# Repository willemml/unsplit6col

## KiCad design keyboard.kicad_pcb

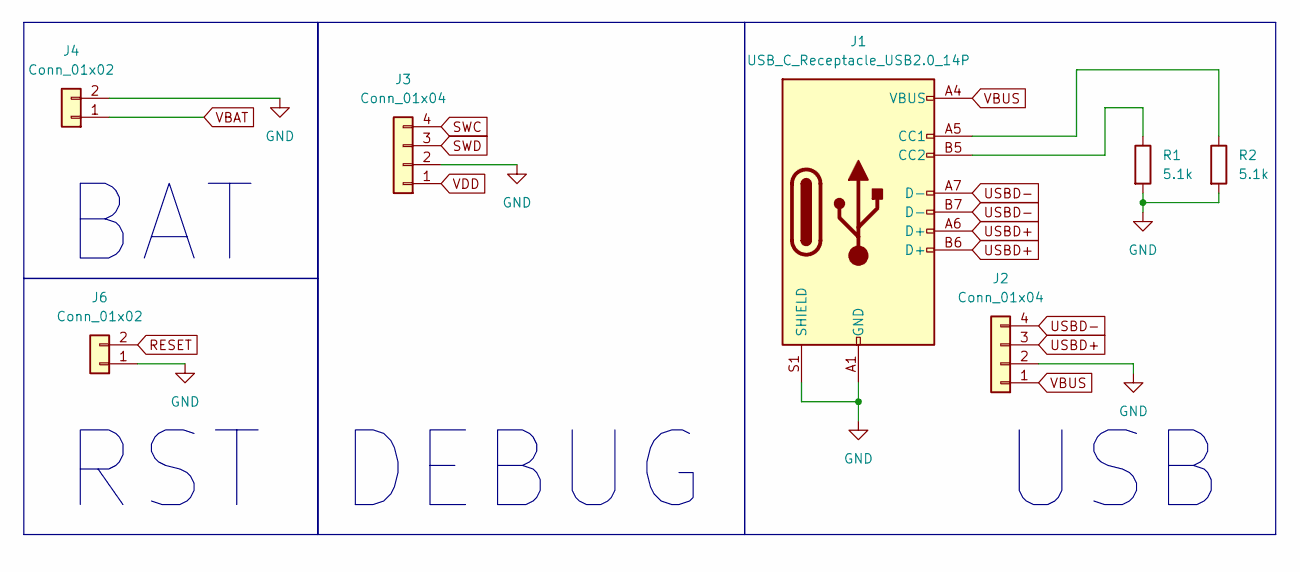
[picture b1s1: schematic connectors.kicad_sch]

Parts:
J1: USB_C_Receptacle_USB2.0_14P; USB_C_Receptacle_HCTL_HC-TYPE-C-16P-01A
J2, J3: Conn_01x04; PinHeader_1x04_P2.54mm_Vertical
J4, J6: Conn_01x02; PinHeader_1x02_P2.54mm_Vertical
R1, R2: 5.1k; R_0603_1608Metric

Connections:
GND: J1.A1 (GND), J1.A12 (GND), J1.B1 (GND), J1.B12 (GND), J1.S1 (SHIELD), J2.2, J3.2, J4.2, J6.1, R1.2, R2.2; also elsewhere on the board
unnamed: J1.A5 (CC1), R2.1
unnamed: J1.B5 (CC2), R1.1
RESET: J6.2; also elsewhere on the board
SWC: J3.4; also elsewhere on the board
SWD: J3.3; also elsewhere on the board
USBD+: J1.A6 (D+), J1.B6 (D+), J2.3; also elsewhere on the board
USBD-: J1.A7 (D-), J1.B7 (D-), J2.4; also elsewhere on the board
VBAT: J4.1; also elsewhere on the board
VBUS: J1.A4 (VBUS), J1.A9 (VBUS), J1.B4 (VBUS), J1.B9 (VBUS), J2.1; also elsewhere on the board
VDD: J3.1; also elsewhere on the board

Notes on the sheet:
USB
RST
BAT
DEBUG

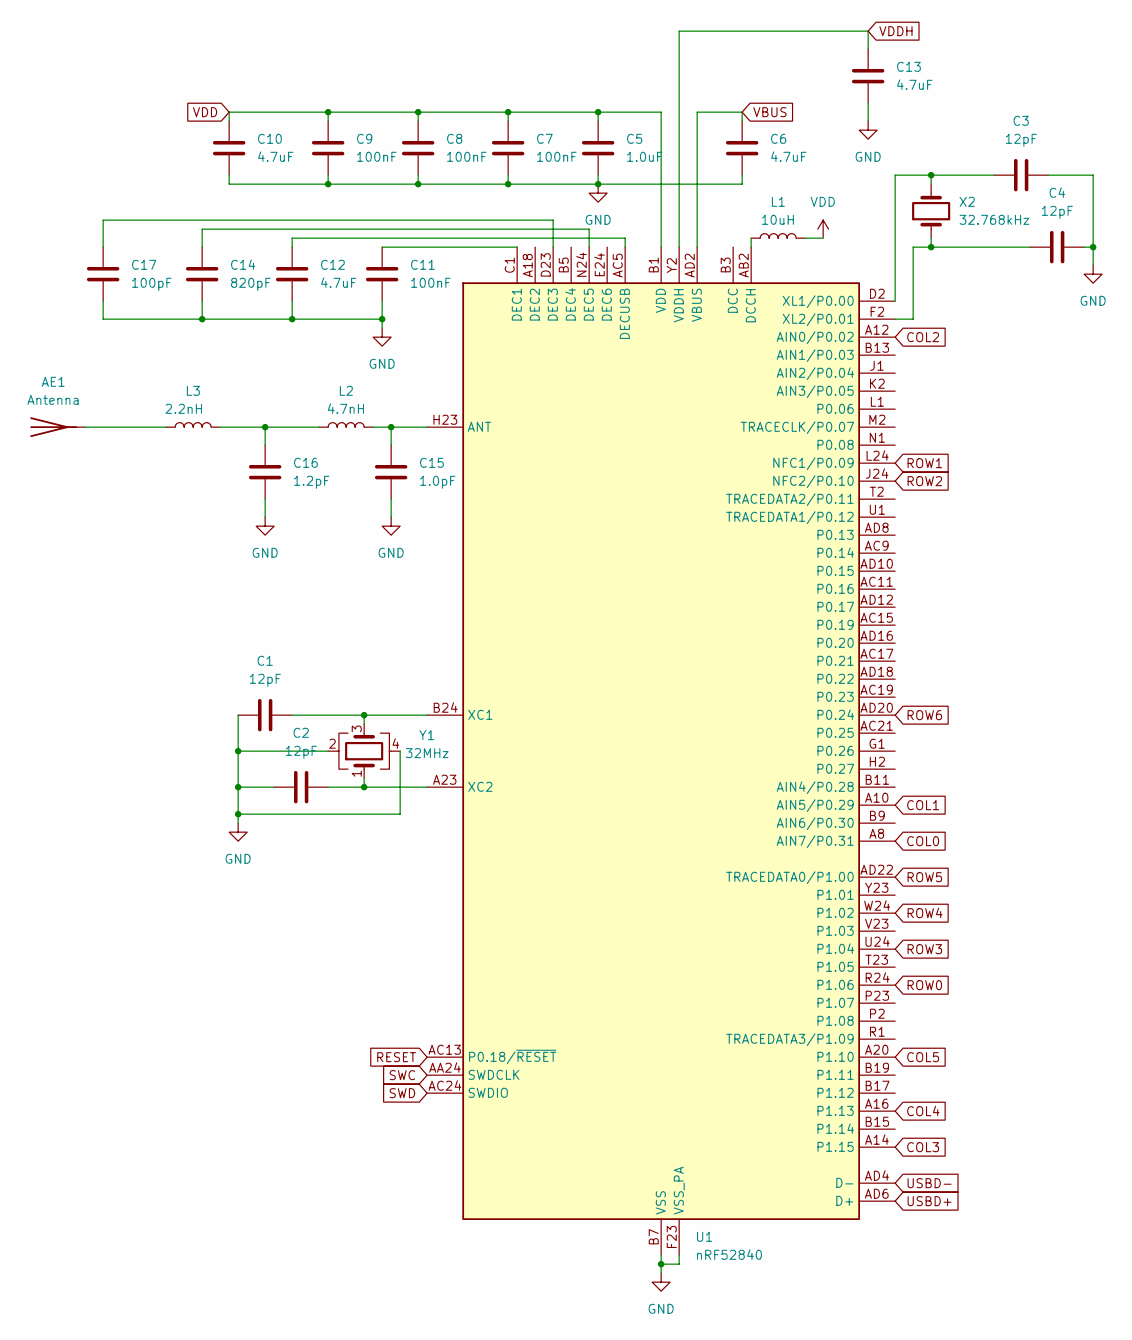
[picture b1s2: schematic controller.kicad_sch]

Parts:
AE1: Antenna; Texas_SWRA117D_2.4GHz_Left
C1, C2, C3, C4: 12pF; C_0603_1608Metric
C5: 1.0uF; C_0603_1608Metric
C6, C10, C12, C13: 4.7uF; C_0603_1608Metric
C7, C8, C9, C11: 100nF; C_0603_1608Metric
C14: 820pF; C_0603_1608Metric
C15: 1.0pF; C_0603_1608Metric
C16: 1.2pF; C_0603_1608Metric
C17: 100pF; C_0603_1608Metric
L1: 10uH; L_0603_1608Metric
L2: 4.7nH; L_0603_1608Metric
L3: 2.2nH; L_0603_1608Metric
U1: nRF52840; Nordic_AQFN-73-1EP_7x7mm_P0.5mm
X2: 32.768kHz; Crystal_SMD_0603-2Pin_6.0x3.5mm; LCSC C182057
Y1: 32MHz; Crystal_SMD_2016-4Pin_2.0x1.6mm; LCSC C2965582

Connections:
COL0: U1.A8 (AIN7/P0.31); also elsewhere on the board
COL1: U1.A10 (AIN5/P0.29); also elsewhere on the board
COL2: U1.A12 (AIN0/P0.02); also elsewhere on the board
COL3: U1.A14 (P1.15); also elsewhere on the board
COL4: U1.A16 (P1.13); also elsewhere on the board
COL5: U1.A20 (P1.10); also elsewhere on the board
GND: C1.1, C2.1, C3.2, C4.2, C5.2, C6.2, C7.2, C8.2, C9.2, C10.2, C11.2, C12.2, C13.2, C14.2, C15.2, C16.2, C17.2, U1.B7 (VSS), U1.EP (VSS), U1.F23 (VSS_PA), Y1.2, Y1.4; also elsewhere on the board
unnamed: AE1.1 (A), L3.1
unnamed: C16.1, L2.1, L3.2
unnamed: C15.1, L2.2, U1.H23 (ANT)
unnamed: L1.1, U1.AB2 (DCCH)
unnamed: C11.1, U1.C1 (DEC1)
unnamed: C17.1, U1.D23 (DEC3)
unnamed: C14.1, U1.N24 (DEC5)
unnamed: C12.1, U1.AC5 (DECUSB)
unnamed: C1.2, U1.B24 (XC1), Y1.3
unnamed: C2.2, U1.A23 (XC2), Y1.1
unnamed: C3.1, U1.D2 (XL1/P0.00), X2.2
unnamed: C4.1, U1.F2 (XL2/P0.01), X2.1
RESET: U1.AC13 (P0.18/~RESET); also elsewhere on the board
ROW0: U1.R24 (P1.06); also elsewhere on the board
ROW1: U1.L24 (NFC1/P0.09); also elsewhere on the board
ROW2: U1.J24 (NFC2/P0.10); also elsewhere on the board
ROW3: U1.U24 (P1.04); also elsewhere on the board
ROW4: U1.W24 (P1.02); also elsewhere on the board
ROW5: U1.AD22 (TRACEDATA0/P1.00); also elsewhere on the board
ROW6: U1.AD20 (P0.24); also elsewhere on the board
SWC: U1.AA24 (SWDCLK); also elsewhere on the board
SWD: U1.AC24 (SWDIO); also elsewhere on the board
USBD+: U1.AD6 (D+); also elsewhere on the board
USBD-: U1.AD4 (D-); also elsewhere on the board
VBUS: C6.1, U1.AD2 (VBUS); also elsewhere on the board
VDD: C5.1, C7.1, C8.1, C9.1, C10.1, L1.2, U1.A22 (VDD), U1.AD14 (VDD), U1.AD23 (VDD), U1.B1 (VDD), U1.W1 (VDD); also elsewhere on the board
VDDH: C13.1, U1.Y2 (VDDH); also elsewhere on the board

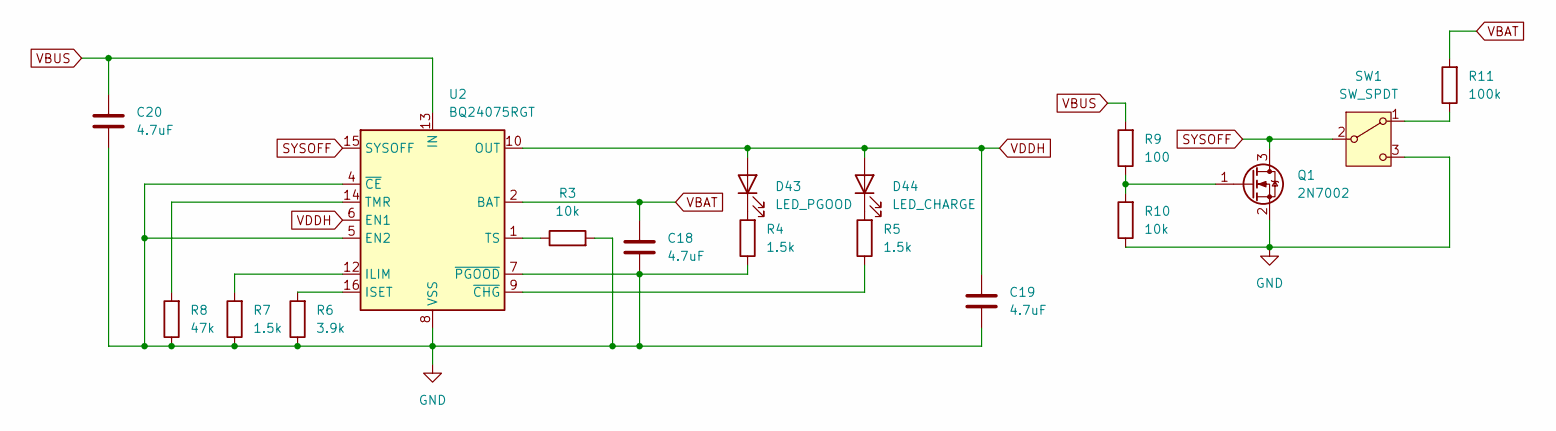
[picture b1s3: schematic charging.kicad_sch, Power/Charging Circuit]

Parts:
C18, C19, C20: 4.7uF; C_0603_1608Metric
D43: LED_PGOOD; LED_0603_1608Metric
D44: LED_CHARGE; LED_0603_1608Metric
Q1: 2N7002; SOT-23
R3, R10: 10k; R_0603_1608Metric
R4, R5, R7: 1.5k; R_0603_1608Metric
R6: 3.9k; R_0603_1608Metric
R8: 47k; R_0603_1608Metric
R9: 100; R_0603_1608Metric
R11: 100k; R_0603_1608Metric
SW1: SW_SPDT; SW_SPDT_PCM12; LCSC C431541
U2: BQ24075RGT; VQFN-16-1EP_3x3mm_P0.5mm_EP1.6x1.6mm

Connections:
GND: C18.2, C19.2, C20.2, Q1.2 (S), R3.2, R4.1, R6.1, R7.1, R8.1, R10.1, SW1.3 (C), U2.4 (~CE), U2.5 (EN2), U2.7 (~PGOOD), U2.8 (VSS), U2.17 (VSS); also elsewhere on the board
unnamed: D43.1 (K), R4.2
unnamed: D44.1 (K), R5.2
unnamed: Q1.1 (G), R9.1, R10.2
unnamed: R11.1, SW1.1 (A)
unnamed: R7.2, U2.12 (ILIM)
unnamed: R6.2, U2.16 (ISET)
unnamed: R8.2, U2.14 (TMR)
unnamed: R3.1, U2.1 (TS)
unnamed: R5.1, U2.9 (~CHG)
SYSOFF: Q1.3 (D), SW1.2 (B), U2.15 (SYSOFF)
VBAT: C18.1, R11.2, U2.2 (BAT), U2.3 (BAT); also elsewhere on the board
VBUS: C20.1, R9.2, U2.13 (IN); also elsewhere on the board
VDDH: C19.1, D43.2 (A), D44.2 (A), U2.6 (EN1), U2.10 (OUT), U2.11 (OUT); also elsewhere on the board

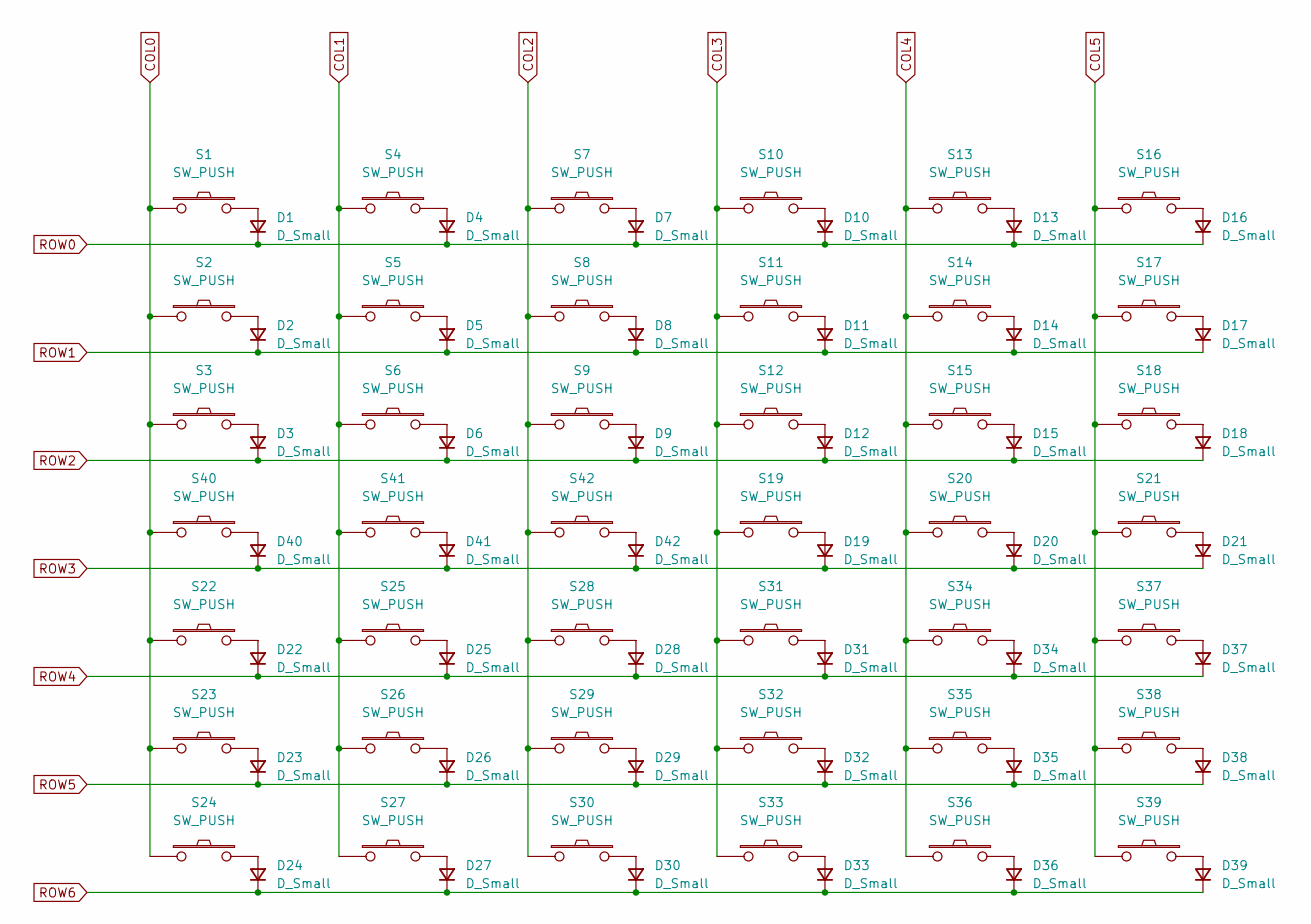
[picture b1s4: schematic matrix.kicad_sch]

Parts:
D1, D2, D3, D4, D5, D6, D7, D8, D9, D10, D11, D12, D13, D14, D15, D16, D17, D18, D19, D20, D21, D22, D23, D24, D25, D26, D27, D28, D29, D30, D31, D32, D33, D34, D35, D36, D37, D38, D39, D40, D41, D42: D_Small; D_SOD-123
S1: SW_PUSH; keyswitch_choc12_hotswap_1u; LCSC C5333465
S2, S3, S4, S5, S6, S7, S8, S9, S10, S11, S12, S13, S14, S15, S16, S17, S18, S19, S20, S21, S22, S23, S24, S25, S26, S27, S28, S29, S30, S31, S32, S33, S34, S35, S36, S37, S38, S39, S40, S41, S42: SW_PUSH; keyswitch_choc12_hotswap_1u

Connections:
COL0: S1.1, S2.1, S3.1, S22.1, S23.1, S24.1, S40.1; also elsewhere on the board
COL1: S4.1, S5.1, S6.1, S25.1, S26.1, S27.1, S41.1; also elsewhere on the board
COL2: S7.1, S8.1, S9.1, S28.1, S29.1, S30.1, S42.1; also elsewhere on the board
COL3: S10.1, S11.1, S12.1, S19.1, S31.1, S32.1, S33.1; also elsewhere on the board
COL4: S13.1, S14.1, S15.1, S20.1, S34.1, S35.1, S36.1; also elsewhere on the board
COL5: S16.1, S17.1, S18.1, S21.1, S37.1, S38.1, S39.1; also elsewhere on the board
unnamed: D1.2 (A), S1.2
unnamed: D2.2 (A), S2.2
unnamed: D3.2 (A), S3.2
unnamed: D4.2 (A), S4.2
unnamed: D5.2 (A), S5.2
unnamed: D6.2 (A), S6.2
unnamed: D7.2 (A), S7.2
unnamed: D8.2 (A), S8.2
unnamed: D9.2 (A), S9.2
unnamed: D10.2 (A), S10.2
unnamed: D11.2 (A), S11.2
unnamed: D12.2 (A), S12.2
unnamed: D13.2 (A), S13.2
unnamed: D14.2 (A), S14.2
unnamed: D15.2 (A), S15.2
unnamed: D16.2 (A), S16.2
unnamed: D17.2 (A), S17.2
unnamed: D18.2 (A), S18.2
unnamed: D19.2 (A), S19.2
unnamed: D20.2 (A), S20.2
unnamed: D21.2 (A), S21.2
unnamed: D22.2 (A), S22.2
unnamed: D23.2 (A), S23.2
unnamed: D24.2 (A), S24.2
unnamed: D25.2 (A), S25.2
unnamed: D26.2 (A), S26.2
unnamed: D27.2 (A), S27.2
unnamed: D28.2 (A), S28.2
unnamed: D29.2 (A), S29.2
unnamed: D30.2 (A), S30.2
unnamed: D31.2 (A), S31.2
unnamed: D32.2 (A), S32.2
unnamed: D33.2 (A), S33.2
unnamed: D34.2 (A), S34.2
unnamed: D35.2 (A), S35.2
unnamed: D36.2 (A), S36.2
unnamed: D37.2 (A), S37.2
unnamed: D38.2 (A), S38.2
unnamed: D39.2 (A), S39.2
unnamed: D40.2 (A), S40.2
unnamed: D41.2 (A), S41.2
unnamed: D42.2 (A), S42.2
ROW0: D1.1 (K), D4.1 (K), D7.1 (K), D10.1 (K), D13.1 (K), D16.1 (K); also elsewhere on the board
ROW1: D2.1 (K), D5.1 (K), D8.1 (K), D11.1 (K), D14.1 (K), D17.1 (K); also elsewhere on the board
ROW2: D3.1 (K), D6.1 (K), D9.1 (K), D12.1 (K), D15.1 (K), D18.1 (K); also elsewhere on the board
ROW3: D19.1 (K), D20.1 (K), D21.1 (K), D40.1 (K), D41.1 (K), D42.1 (K); also elsewhere on the board
ROW4: D22.1 (K), D25.1 (K), D28.1 (K), D31.1 (K), D34.1 (K), D37.1 (K); also elsewhere on the board
ROW5: D23.1 (K), D26.1 (K), D29.1 (K), D32.1 (K), D35.1 (K), D38.1 (K); also elsewhere on the board
ROW6: D24.1 (K), D27.1 (K), D30.1 (K), D33.1 (K), D36.1 (K), D39.1 (K); also elsewhere on the board

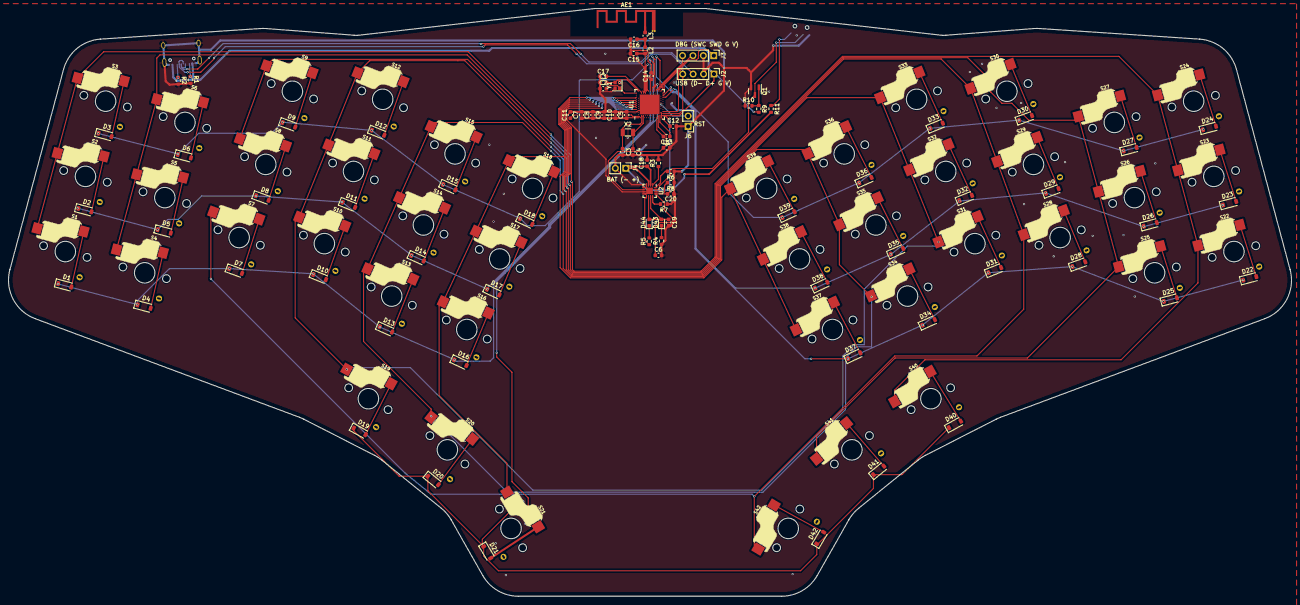
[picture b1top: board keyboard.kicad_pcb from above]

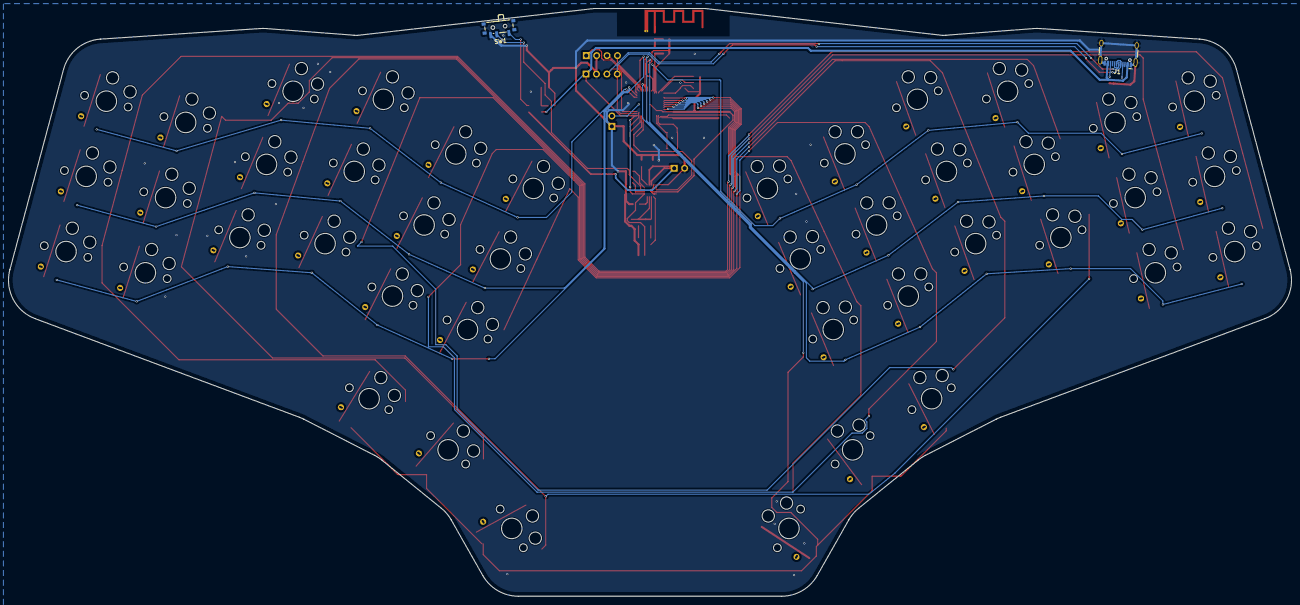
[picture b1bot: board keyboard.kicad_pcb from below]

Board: 2 copper layers, 313.2 x 143.5 mm, 132 parts (2 on the bottom side), 89 nets.

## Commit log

2024-02-28 Initializes project repository
2024-02-29 Adds ergogen outputs
2024-03-04 Start routing antennna
2024-03-06 Change board shape
2024-03-06 Route CPU and charging circuit
2024-03-06 Route rows and columns
2024-03-06 Add ground fill
2024-03-12 first jlc submission
